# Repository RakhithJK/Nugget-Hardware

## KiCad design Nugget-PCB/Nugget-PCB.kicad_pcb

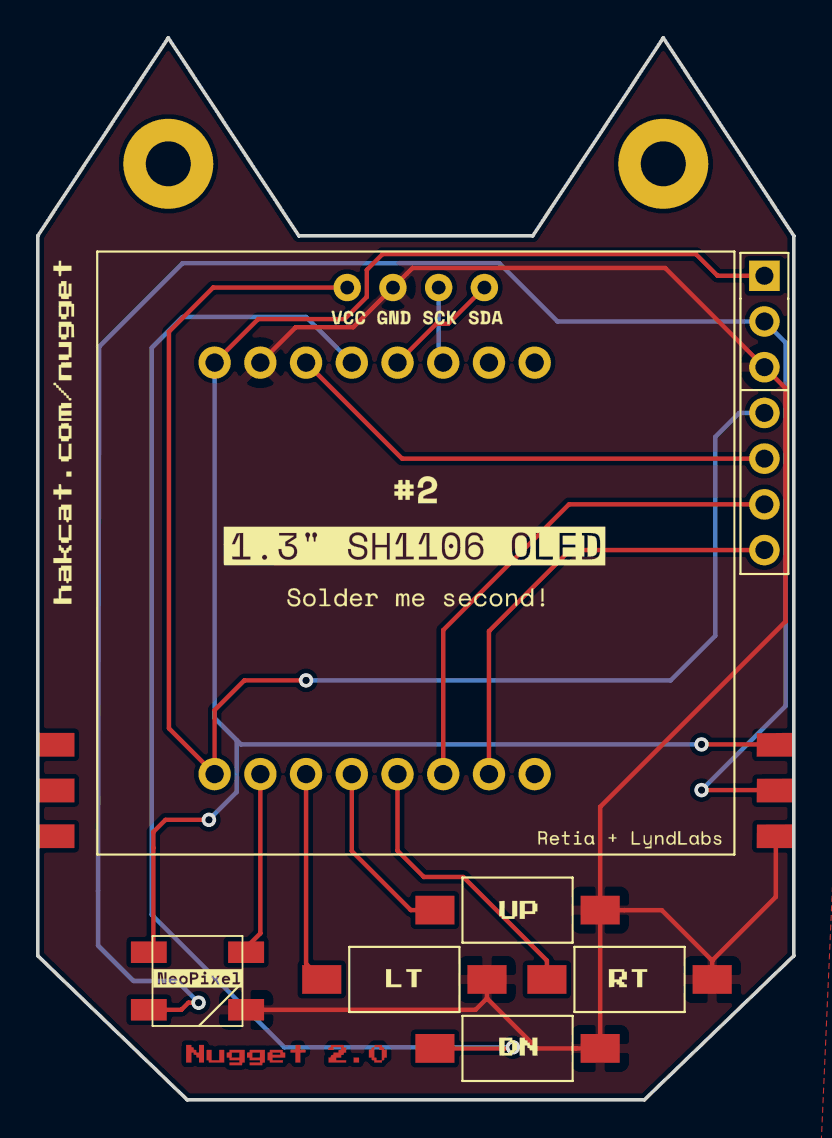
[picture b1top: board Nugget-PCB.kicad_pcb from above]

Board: 2 copper layers, 42.0 x 59.0 mm, 7 parts (1 on the bottom side), 10 nets.

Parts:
Brd1: SH1106; SH1106-128x64-OLED
D1: WS2812B; LED_WS2812B_PLCC4_5.0x5.0mm_P3.2mm_idiot_proof
SW1: Up; SW_SPST_FSMSM
SW2: Down; SW_SPST_FSMSM
SW3: Left; SW_SPST_FSMSM
SW4: Right; SW_SPST_FSMSM
U1: WeMos D1 Mini; wemos-d1-mini-with-pin-header-and-connector

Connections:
+5V: D1.1, U1.9
/D5: SW4.1, U1.4
/D6: SW1.1, U1.5
/D7: SW3.1, U1.6
GND: Brd1.2, D1.3, SW1.2, SW2.2, SW3.2, SW4.2, U1.10
unnamed: Brd1.1, U1.8
unnamed: Brd1.3, U1.14
unnamed: Brd1.4, U1.13
unnamed: D1.4, U1.7
unnamed: SW2.1, U1.12

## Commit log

2021-09-11 version 2.0
2021-09-12 test version 3.0
2021-09-13 initialize new branch
